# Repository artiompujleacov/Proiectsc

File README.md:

# README - OpenBook E-Reader

**Autor: Artiom Pujleacov**

## Prezentare Generală

OpenBook este un dispozitiv e-reader open-source, bazat pe microcontrollerul ESP32-C6. Acesta integrează un ecran e-paper de 7.5 inch, senzori de mediu (BME680), un sistem de gestionare a bateriei și conectivitate prin Wi-Fi și USB-C. Acest document oferă detalii despre arhitectura hardware, componentele utilizate și conexiunile lor.

---

## Diagramă de Bloc

# Lista de componente

| Cantitate | Componentă                         | Valoare | Descriere                                 | Carcasă                         | Reper        | Link Cumpărare                                                                 | Datasheet                                                                          |
|-----------|------------------------------------|---------|-------------------------------------------|---------------------------------|--------------|----------------------------------------------------------------------------------|------------------------------------------------------------------------------------|
| 1         | ADAFRUIT_LEDCHIP-LED0603           | -       | LED                                       | ADAFRUIT_CHIP-LED0603           | CHG_LED      | [link](https://www.mouser.com/ProductDetail/Adafruit/CHIP-LED0603)               | [datasheet](https://www.mouser.com/datasheet/2/737/CHIP-LED0603-1877199.pdf)       |
| 1         | SJ                                 | -       | SMD solder JUMPER                         | SJ                              | SJ1          | [link](https://www.mouser.com/ProductDetail/TE-Connectivity/1-2176091-2)         | [datasheet](https://www.mouser.com/datasheet/2/418/1-2176091-2-1817091.pdf)        |
| 1         | ESP32_WROVER_EAGLE-LTSPICE_RR0402  | 0.47Ω   | Rezistor                                  | ESP32_WROVER_EAGLE-LTSPICE_R0402| R3           | [link](https://www.mouser.com/ProductDetail/Vishay/CRCW04020047ZRT7)             | [datasheet](https://www.mouser.com/datasheet/2/427/crcwce-1764191.pdf)             |
| 1         | ESP32_WROVER_EAGLE-LTSPICE_RR0402  | 100KΩ   | Rezistor                                  | ESP32_WROVER_EAGLE-LTSPICE_R0402| R1_PWRUSB    | [link](https://www.mouser.com/ProductDetail/Vishay/CRCW0402100KFKED)             | [datasheet](https://www.mouser.com/datasheet/2/427/crcwce-1764191.pdf)             |
| 8         | EAGLE-LTSPICE_CC0402               | 100nF   | Condensator                               | EAGLE-LTSPICE_C0402             | C1, C2, C4_USB, C6, C8, C9, C10, C_DELAY | [link](https://www.mouser.com/ProductDetail/Murata/GRM155R71C104KA88D)            | [datasheet](https://www.mouser.com/datasheet/2/281/GRM155R71C104KA88D-1767201.pdf) |
| 1         | RCL_CPOL-EUCT3528                  | 100µF   | Condensator polarizat                     | RCL_CT3528                      | C3           | [link](https://www.mouser.com/ProductDetail/Panasonic/EEE-FK1V101P)              | [datasheet](https://www.mouser.com/datasheet/2/315/EEE-FK1V101P-1526881.pdf)       |
| 10        | ESP32_WROVER_EAGLE-LTSPICE_RR0402  | 10KΩ    | Rezistor                                  | ESP32_WROVER_EAGLE-LTSPICE_R0402| R1, R1-PINH, R1_PINH1, R2-PINH, R2_PINH1, R4, R_BOOT, R_CHANGE, R_CL1, R_RESET | [link](https://www.mouser.com/ProductDetail/Vishay/CRCW040210K0FKED)              | [datasheet](https://www.mouser.com/datasheet/2/427/crcwce-1764191.pdf)             |
| 6         | ESP32_WROVER_EAGLE-LTSPICE_RR0402  | 10kΩ    | Rezistor                                  | ESP32_WROVER_EAGLE-LTSPICE_R0402| R5, R6, R7, R8, R9, R10 | [link](https://www.mouser.com/ProductDetail/Vishay/CRCW040210K0FKED)              | [datasheet](https://www.mouser.com/datasheet/2/427/crcwce-1764191.pdf)             |
| 1         | EAGLE-LTSPICE_CC0402               | 10µF    | Condensator                               | EAGLE-LTSPICE_C0402             | C7           | [link](https://www.mouser.com/ProductDetail/Murata/GRM155R61A106ME44D)           | [datasheet](https://www.mouser.com/datasheet/2/281/GRM155R61A106ME44D-1767201.pdf) |
| 1         | 112A-TAAR-R03_ATTEND               | -       | Micro SD Card Socket, Push-Push Type      | 112ATAARR03ATTEND               | J4           | [link](https://www.mouser.com/ProductDetail/Attend/112A-TAAR-R03)                | [datasheet](https://www.mouser.com/datasheet/2/828/112A-TAAR-R03-1222862.pdf)      |
| 1         | ESP32_WROVER_EAGLE-LTSPICE_RR0402  | 15Ω     | Rezistor                                  | ESP32_WROVER_EAGLE-LTSPICE_R0402| R_CAPACITOR  | [link](https://www.mouser.com/ProductDetail/Vishay/CRCW040215R0FKED)             | [datasheet](https://www.mouser.com/datasheet/2/427/crcwce-1764191.pdf)             |
| 1         | EAGLE-LTSPICE_CC0402               | 1µF     | Condensator                               | EAGLE-LTSPICE_C0402             | C5           | [link](https://www.mouser.com/ProductDetail/Murata/GRM155R61A105KE15D)           | [datasheet](https://www.mouser.com/datasheet/2/281/GRM155R61A105KE15D-1767201.pdf) |
| 10        | EAGLE-LTSPICE_CC0402               | 1µF/50V | Condensator ceramic multi-strat           | 0402                           | EPD_C1, EPD_C2, EPD_C5, EPD_C6, EPD_C7, EPD_C8, EPD_C9, EPD_C10, EPD_C11, EPD_C12 | [link](https://www.mouser.com/ProductDetail/Murata-Electronics/GRM155R61A105KE15D) | [datasheet](https://www.mouser.com/datasheet/2/281/1/GRM155R61A105KE15_01A-1983730.pdf) |

---

## Detalii Hardware

### ESP32-C6-WROOM-1-N8

- **Rol**: Control principal, suport pentru conectivitate wireless și periferice.
- **Interfețe disponibile**:
  - SPI: Display e-paper, memorie Flash, card Micro SD.
  - I2C: Senzor BME680, monitorizare baterie (MAX17048), ceas RTC (DS3231).
  - GPIO: Interacțiune cu butoane și LED-uri.
  - UART: Debugging și conectivitate serială.
- **Specificații**: 160MHz, 512KB SRAM, 8MB Flash integrat.

### Display E-Paper

- **Caracteristici**: Dimensiune 7.5 inch, rezoluție 800x480 pixeli, contrast 8:1.
- **Conectivitate**: Utilizare prin interfață SPI cu linii dedicate pentru control și resetare.
- **Consum**: <50mA în timpul actualizării imaginii, aproape nul în mod standby.

### Senzor BME680

- **Funcționalitate**: Măsurători de temperatură, umiditate, presiune atmosferică și calitate a aerului.
- **Interfață**: Conectare prin magistrala I2C la 400kHz.
- **Consum**: Sub 1mA în activitate, sub 1µA în modul de repaus.

### Sistem de Alimentare

- **Baterie**: Li-Po de 2500mAh, 3.7V.
- **Încărcare**: Controlată de MCP73831 prin portul USB-C, cu o capacitate maximă de 1A.
- **Monitorizare**: Funcție asigurată de MAX17048, comunicare prin I2C.
- **Consum energetic**:
  - Activ (Wi-Fi + ecran actualizat): ~150mA.
  - Standby (doar ecran afișat): ~10mA.
  - Deep Sleep: Sub 50µA.
  - **Autonomie estimată**: Aproximativ o săptămână (~250 ore cu un consum mediu de 10mA).

### Butoane de Navigare

- Echipate cu butoane tactile Panasonic EVQPUJ02K, fiecare având o rezistență pull-up de 10KΩ.

### USB-C

- **Rol**: Funcționează atât pentru încărcare (5V/1A), cât și pentru transfer de date (USB 2.0).
- **Protecție**: Integrare de diode ESD (USBLC6-2SC6Y) pentru siguranță la supratensiune.

---

## Configurare Pini ESP32-C6

| **Pin ESP32-C6** | **Funcție**         | **Componentă**         | **Rol**                                    |
|------------------|--------------------|------------------------|--------------------------------------------|
| GPIO0           | BOOT_BUTTON        | Buton                  | Mod boot la inițializare                   |
| GPIO1           | RESET_BUTTON       | Buton                  | Reset manual                               |
| GPIO2           | CHANGE_BUTTON      | Buton                  | Schimbare meniuri                          |
| GPIO3           | EPD_CS             | Display E-Paper        | Chip Select pentru SPI                     |
| GPIO4           | EPD_DC             | Display E-Paper        | Control Date/Comenzi                       |
| GPIO5           | EPD_RST            | Display E-Paper        | Reset display                              |
| GPIO6           | EPD_BUSY           | Display E-Paper        | Detectare stare refresh                    |
| GPIO7           | SPI_MOSI           | Display, Flash, SD     | Linii de date SPI                          |
| GPIO8           | SPI_MISO           | Display, Flash, SD     | Linie de date SPI (citire)                 |
| GPIO9           | SPI_SCK            | Display, Flash, SD     | Semnal de ceas SPI                         |
| GPIO10          | FLASH_CS           | Memorie Flash          | Chip Select pentru memorie                 |
| GPIO11          | SD_CS              | Card Micro SD          | Chip Select pentru card SD                 |
| GPIO12          | I2C_SDA            | BME680, MAX17048, DS3231 | Linie de date pentru I2C                   |
| GPIO13          | I2C_SCL            | BME680, MAX17048, DS3231 | Linie de ceas pentru I2C                   |
| GPIO14          | CHG_LED            | LED                    | Indică procesul de încărcare               |
| GPIO15          | UART_TX            | Debugging              | Transmitere date seriale                    |
| GPIO16          | UART_RX            | Debugging              | Recepție date seriale                       |
| GPIO17          | USB_D+             | USB-C                  | Linie de date USB pozitivă                  |
| GPIO18          | USB_D-             | USB-C                  | Linie de date USB negativă                  |

**Notă**: Pinii sunt selectați conform specificațiilor ESP32-C6 și funcționalităților necesare dispozitivului OpenBook. Unele dintre aceștia sunt multifuncționali și pot fi reutilizați în diverse configurații.

---

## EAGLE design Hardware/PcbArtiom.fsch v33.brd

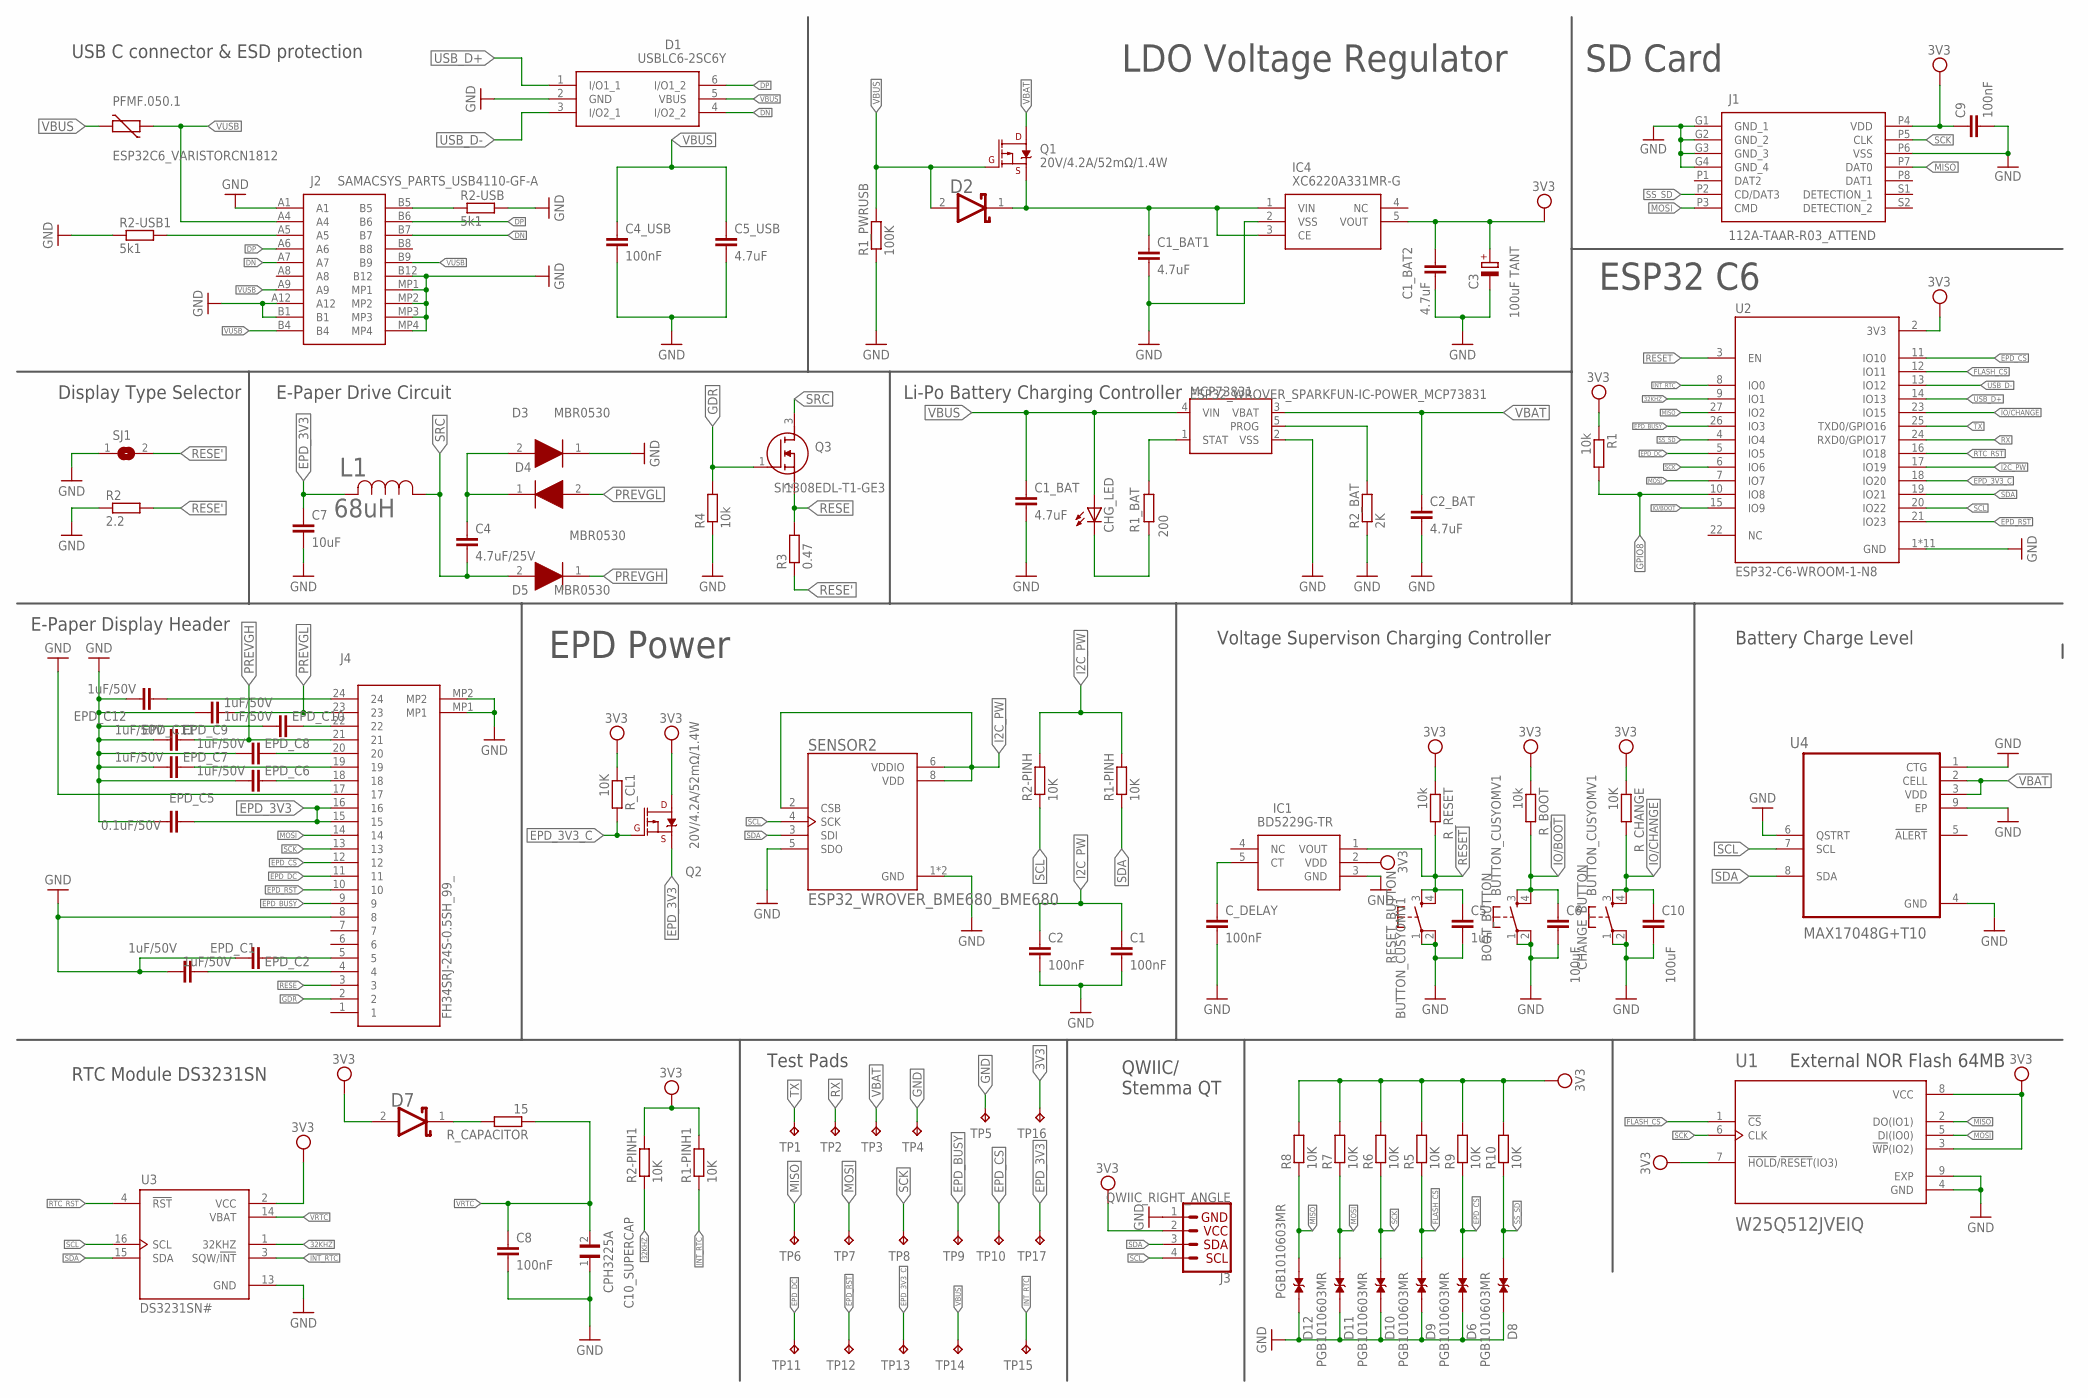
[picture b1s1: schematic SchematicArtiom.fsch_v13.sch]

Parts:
BOOT_BUTTON: BUTTON_CUSYOMV1; MYBUTTON
C1, C2, C4_USB, C8: 100nF; ESP32_WROVER_EAGLE-LTSPICE_C0402
C1_BAT, C2_BAT, C5_USB: 4.7uF; ESP32_WROVER_EAGLE-LTSPICE_C0402
C1_BAT1, C1_BAT2: 4.7uF; EAGLE-LTSPICE_C0402
C3: 100uF TANT; RCL_CT3528
C4: 4.7uF/25V; ESP32_WROVER_EAGLE-LTSPICE_C0402
C5: 1uF; ESP32_WROVER_EAGLE-LTSPICE_C0402
C6, C10: 100uF; ESP32_WROVER_EAGLE-LTSPICE_C0402
C7: 10uF; ESP32_WROVER_EAGLE-LTSPICE_C0402
C9: 100nF; EAGLE-LTSPICE_C0402
C10_SUPERCAP: CPH3225A; CAPCP3225X100N
CHANGE_BUTTON: BUTTON_CUSYOMV1; MYBUTTON
CHG_LED: ADAFRUIT_LEDCHIP-LED0603; ADAFRUIT_CHIP-LED0603
C_DELAY: 100nF; EAGLE-LTSPICE_C0402
D1: USBLC6-2SC6Y; SOT95P280X145-6N
D2, D7: ESP32_WROVER_AVX---SD0805S020S1R0_AVX_SD0805S020S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; ESP32_WROVER_AVX---SD0805S020S1R0_AVX_SD0805S020S1R0_0
D3, D4, D5: MBR0530; SOD3716X135N
D6, D8, D9, D10, D11, D12: PGB1010603MR; DIOC1608X36N
EPD_C1, EPD_C2, EPD_C6, EPD_C7, EPD_C8, EPD_C9, EPD_C10, EPD_C11, EPD_C12: 1uF/50V; ESP32_WROVER_EAGLE-LTSPICE_C0402
EPD_C5: 0.1uF/50V; ESP32_WROVER_EAGLE-LTSPICE_C0402
IC1: BD5229G-TR; SOT95P280X125-5N
IC4: XC6220A331MR-G; SOT95P280X120-5N
J1: 112A-TAAR-R03_ATTEND; 112ATAARR03ATTEND
J2: SAMACSYS_PARTS_USB4110-GF-A; SAMACSYS_PARTS_USB4110GFA
J3: QWIIC_RIGHT_ANGLE; JST04_1MM_RA
J4: FH34SRJ-24S-0.5SH_99_; FH34SRJ24S05SH99
L1: 68uH; IND_4828-WE-TPC_WRE
MCP73831: ESP32_WROVER_SPARKFUN-IC-POWER_MCP73831; ESP32_WROVER_SPARKFUN-IC-POWER_SOT23-5
PFMF.050.1: ESP32C6_VARISTORCN1812; ESP32C6_VARISTOR_CT/CN1812
Q1, Q2: 20V/4.2A/52mΩ/1.4W; ESP32_WROVER_SPARKFUN-DISCRETESEMI_SOT23-3
Q3: SI1308EDL-T1-GE3; SOT65P210X110-3N
R1, R4: 10k; ESP32_WROVER_EAGLE-LTSPICE_R0402
R1-PINH, R1-PINH1, R2-PINH, R2-PINH1, R5, R6, R7, R8, R9, R10: 10K; ESP32_WROVER_EAGLE-LTSPICE_R0402
R1_BAT: 200; ESP32_WROVER_EAGLE-LTSPICE_R0402
R1_PWRUSB: 100K; ESP32_WROVER_EAGLE-LTSPICE_R0402
R2: 2.2; ESP32_WROVER_EAGLE-LTSPICE_R0402
R2-USB, R2-USB1: 5k1; ESP32_WROVER_EAGLE-LTSPICE_R0402
R2_BAT: 2K; ESP32_WROVER_EAGLE-LTSPICE_R0402
R3: 0.47; ESP32_WROVER_EAGLE-LTSPICE_R0402
RESET_BUTTON: BUTTON_CUSYOMV1; MYBUTTON
R_BOOT: 10k; ESP32_WROVER_EAGLE-LTSPICE_R0402
R_CAPACITOR: 15; ESP32_WROVER_EAGLE-LTSPICE_R0402
R_CHANGE: 10K; ESP32_WROVER_EAGLE-LTSPICE_R0402
R_CL1: 10K; ESP32_WROVER_EAGLE-LTSPICE_R0402
R_RESET: 10k; ESP32_WROVER_EAGLE-LTSPICE_R0402
SENSOR2: ESP32_WROVER_BME680_BME680; ESP32_WROVER_BME680_PSON80P300X300X100-8N
SJ1: SJ
TP1, TP2, TP3, TP4, TP5, TP6, TP7, TP8, TP9, TP10, TP11, TP12, TP13, TP14, TP15, TP16, TP17: TPTP20R; TP20R
U1: W25Q512JVEIQ; SON127P600X800X80-9N
U2: ESP32-C6-WROOM-1-N8; XCVR_ESP32-C6-WROOM-1-N8
U3: DS3231SN#; SOIC127P1032X265-16N
U4: MAX17048G+T10; SON50P200X200X80-9N

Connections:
3V3: C1_BAT2.1, C3.+, C9.1, D7.2 (ANODE), IC1.2 (VDD), IC4.5 (VOUT), J1.P4 (VDD), J3.2, Q2.3 (D), R1.1, R1-PINH1.2, R2-PINH1.2, R5.2, R6.2, R7.2, R8.2, R9.2, R10.2, R_BOOT.1, R_CHANGE.1, R_CL1.1, R_RESET.1, TP16.TP, U1.3 (!WP!(IO2)), U1.7 (!HOLD!/!RESET!(IO3)), U1.8 (VCC), U2.2 (3V3), U3.2 (VCC)
32KHZ: R2-PINH1.1, U2.9 (IO1), U3.1 (32KHZ)
DN: D1.4 (I/O2_2), J2.A7, J2.B7
DP: D1.6 (I/O1_2), J2.A6, J2.B6
EPD_3V3: C7.1, EPD_C5.1, J4.15, J4.16, L1.2, Q2.2 (S), TP17.TP
EPD_3V3_C: Q2.1 (G), R_CL1.2, TP13.TP, U2.18 (IO20)
EPD_BUSY: J4.9, TP9.TP, U2.26 (IO3)
EPD_CS: D6.2, J4.12, R9.1, TP10.TP, U2.11 (IO10)
EPD_DC: J4.11, TP11.TP, U2.5 (IO5)
EPD_RST: J4.10, TP12.TP, U2.21 (IO23)
FLASH_CS: D9.2, R5.1, U1.1 (!CS), U2.12 (IO11)
GDR: J4.2, Q3.1 (G), R4.2
GND: BOOT_BUTTON.1, BOOT_BUTTON.2, C1.2, C1_BAT.2, C1_BAT1.2, C1_BAT2.2, C2.2, C2_BAT.2, C3.-, C4_USB.2, C5.2, C5_USB.2, C6.2, C7.2, C8.2, C9.2, C10.2, C10_SUPERCAP.1, CHANGE_BUTTON.1, CHANGE_BUTTON.2, C_DELAY.2, D1.2 (GND), D3.1 (K), D6.1, D8.1, D9.1, D10.1, D11.1, D12.1, EPD_C1.2, EPD_C2.2, EPD_C5.2, EPD_C6.2, EPD_C7.2, EPD_C8.2, EPD_C9.2, EPD_C10.2, EPD_C11.2, EPD_C12.2, IC1.3 (GND), IC4.2 (VSS), J1.G1 (GND_1), J1.G2 (GND_2), J1.G3 (GND_3), J1.G4 (GND_4), J1.P6 (VSS), J2.A1, J2.A12, J2.B1, J2.B12, J2.MP1, J2.MP2, J2.MP3, J2.MP4, J3.1, J4.8, J4.17, J4.MP1, J4.MP2, MCP73831.2 (VSS), R1_PWRUSB.1, R2.1, R2-USB.2, R2-USB1.1, R2_BAT.1, R4.1, RESET_BUTTON.1, RESET_BUTTON.2, SENSOR2.1 (GND), SENSOR2.5 (SDO), SENSOR2.7 (GND), SJ1.1, TP4.TP, TP5.TP, U1.4 (GND), U1.9 (EXP), U2.1 (GND), U2.28 (GND), U2.29_1 (GND), U2.29_2 (GND), U2.29_3 (GND), U2.29_4 (GND), U2.29_5 (GND), U2.29_6 (GND), U2.29_7 (GND), U2.29_8 (GND), U2.29_9 (GND), U3.13 (GND), U4.1 (CTG), U4.4 (GND), U4.6 (QSTRT), U4.9 (EP)
GPIO8: R1.2, U2.10 (IO8)
I2C_PW: C1.1, C2.1, R1-PINH.2, R2-PINH.2, SENSOR2.2 (CSB), SENSOR2.6 (VDDIO), SENSOR2.8 (VDD), U2.17 (IO19)
INT_RTC: R1-PINH1.1, TP15.TP, U2.8 (IO0), U3.3 (SQW/!INT)
IO/BOOT: BOOT_BUTTON.3, BOOT_BUTTON.4, C6.1, R_BOOT.2, U2.15 (IO9)
IO/CHANGE: C10.1, CHANGE_BUTTON.3, CHANGE_BUTTON.4, R_CHANGE.2, U2.23 (IO15)
MISO: D12.2, J1.P7 (DAT0), R8.1, TP6.TP, U1.2 (DO(IO1)), U2.27 (IO2)
MOSI: D11.2, J1.P3 (CMD), J4.14, R7.1, TP7.TP, U1.5 (DI(IO0)), U2.7 (IO7)
unnamed: C1_BAT1.1, D2.1 (CATHODE), IC4.1 (VIN), IC4.3 (CE), Q1.2 (S)
unnamed: MCP73831.1 (STAT), R1_BAT.1
unnamed: CHG_LED.C, R1_BAT.2
unnamed: J2.B5, R2-USB.1
unnamed: MCP73831.5 (PROG), R2_BAT.2
unnamed: D7.1 (CATHODE), R_CAPACITOR.2
unnamed: C_DELAY.1, IC1.5 (CT)
unnamed: EPD_C2.1, J4.5
unnamed: J2.A5, R2-USB1.2
unnamed: EPD_C1.1, J4.4
unnamed: EPD_C6.1, J4.18
unnamed: EPD_C7.1, J4.19
unnamed: EPD_C8.1, J4.20
unnamed: EPD_C10.1, J4.22
unnamed: EPD_C12.1, J4.24
unnamed: C4.1, D3.2 (A), D4.1 (K)
PREVGH: D5.1 (K), EPD_C9.1, J4.21
PREVGL: D4.2 (A), EPD_C11.1, J4.23
RESE: J4.3, Q3.2 (S), R3.2
RESE': R2.2, R3.1, SJ1.2
RESET: C5.1, IC1.1 (VOUT), RESET_BUTTON.3, RESET_BUTTON.4, R_RESET.2, U2.3 (EN)
RTC_RST: U2.16 (IO18), U3.4 (!RST)
RX: TP2.TP, U2.24 (RXD0/GPIO17)
SCK: D10.2, J1.P5 (CLK), J4.13, R6.1, TP8.TP, U1.6 (CLK), U2.6 (IO6)
SCL: J3.4, R2-PINH.1, SENSOR2.4 (SCK), U2.20 (IO22), U3.16 (SCL), U4.7 (SCL)
SDA: J3.3, R1-PINH.1, SENSOR2.3 (SDI), U2.19 (IO21), U3.15 (SDA), U4.8 (SDA)
SRC: C4.2, D5.2 (A), L1.1, Q3.3 (D)
SS_SD: D8.2, J1.P2 (CD/DAT3), R10.1, U2.4 (IO4)
TX: TP1.TP, U2.25 (TXD0/GPIO16)
USB_D+: D1.1 (I/O1_1), U2.14 (IO13)
USB_D-: D1.3 (I/O2_1), U2.13 (IO12)
VBAT: C2_BAT.1, MCP73831.3 (VBAT), Q1.3 (D), TP3.TP, U4.2 (CELL), U4.3 (VDD)
VBUS: C1_BAT.1, C4_USB.1, C5_USB.1, CHG_LED.A, D1.5 (VBUS), D2.2 (ANODE), MCP73831.4 (VIN), PFMF.050.1.2, Q1.1 (G), R1_PWRUSB.2, TP14.TP
VRTC: C8.1, C10_SUPERCAP.2, R_CAPACITOR.1, U3.14 (VBAT)
VUSB: J2.A4, J2.A9, J2.B4, J2.B9, PFMF.050.1.1

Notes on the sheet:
SD Card
ESP32 C6
LDO Voltage Regulator
Li-Po Battery Charging Controller
E-Paper Drive Circuit
EPD Power
USB C connector & ESD protection
Display Type Selector
E-Paper Display Header
Voltage Supervison Charging Controller
Battery Charge Level
External NOR Flash 64MB
QWIIC/ Stemma QT
Test Pads
RTC Module DS3231SN

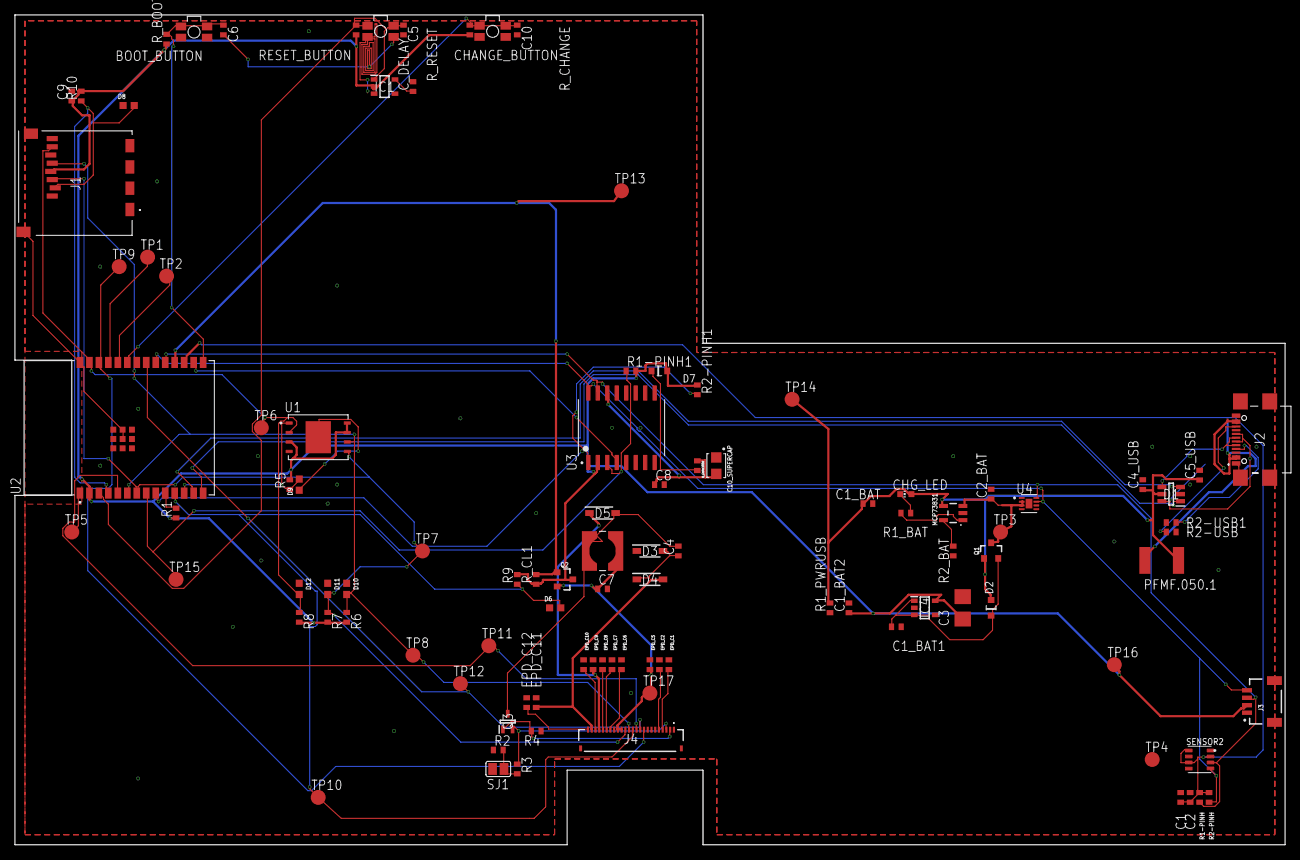
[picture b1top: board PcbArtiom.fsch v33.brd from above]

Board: 2 copper layers, 170.2 x 111.2 mm, 103 parts (0 on the bottom side), 55 nets.

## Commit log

2025-04-06 Rename LICENSE.md to LICENSE

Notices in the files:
parts and their libraries:
COPYRIGHT: Copyright (C) 2024 Ultra Librarian. All rights reserved.
